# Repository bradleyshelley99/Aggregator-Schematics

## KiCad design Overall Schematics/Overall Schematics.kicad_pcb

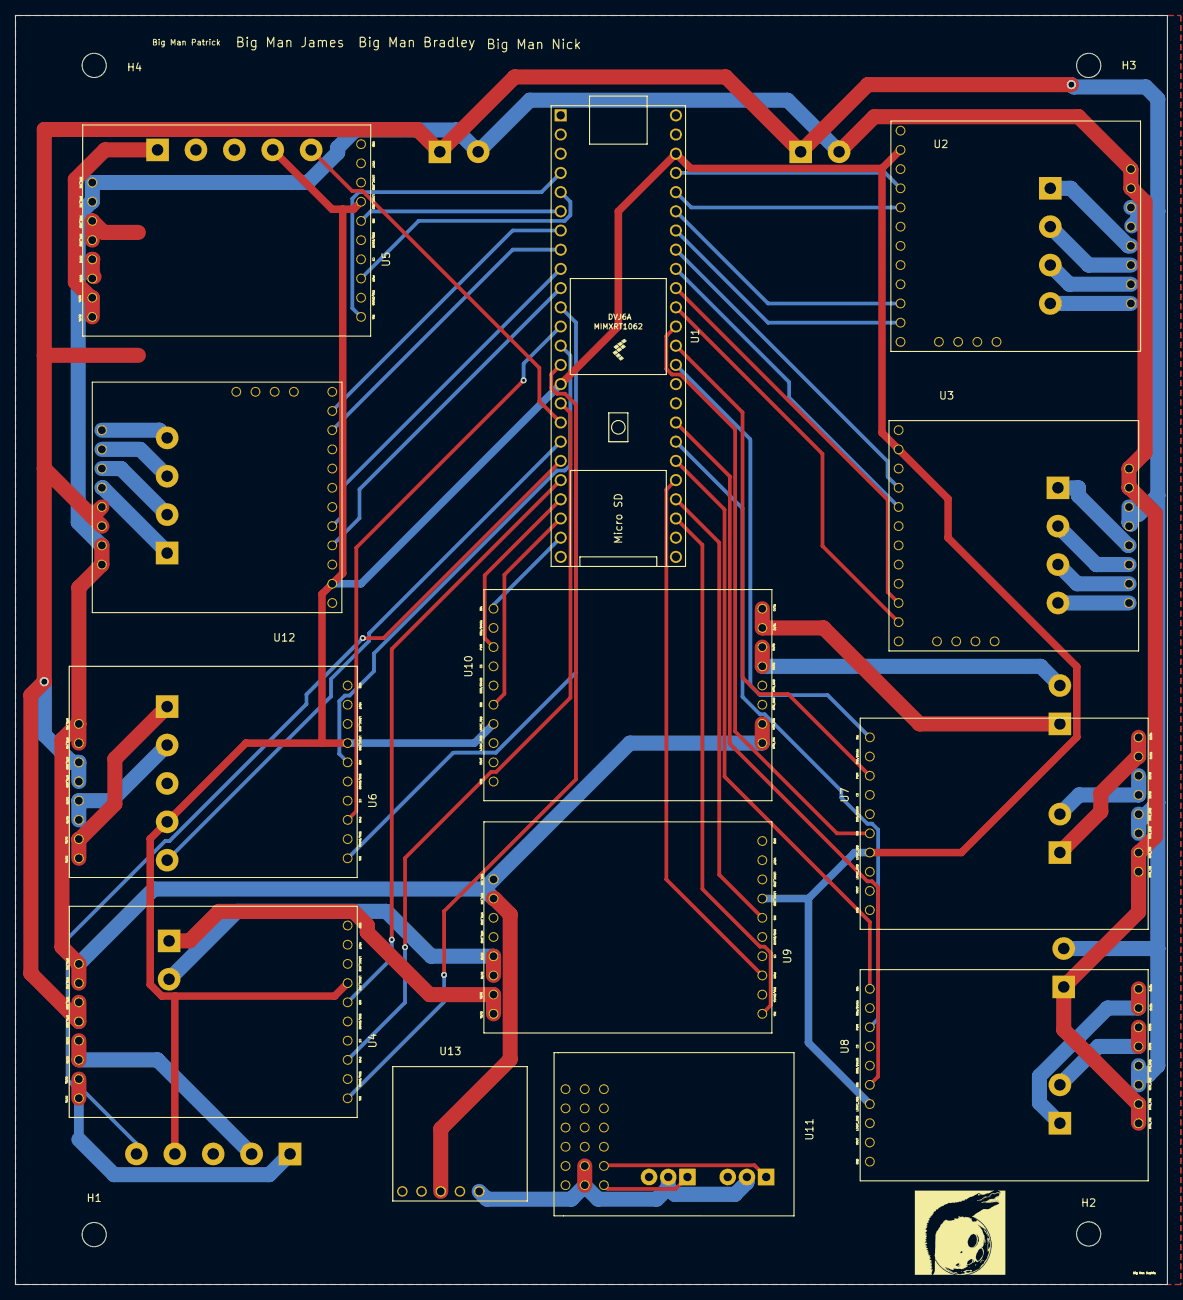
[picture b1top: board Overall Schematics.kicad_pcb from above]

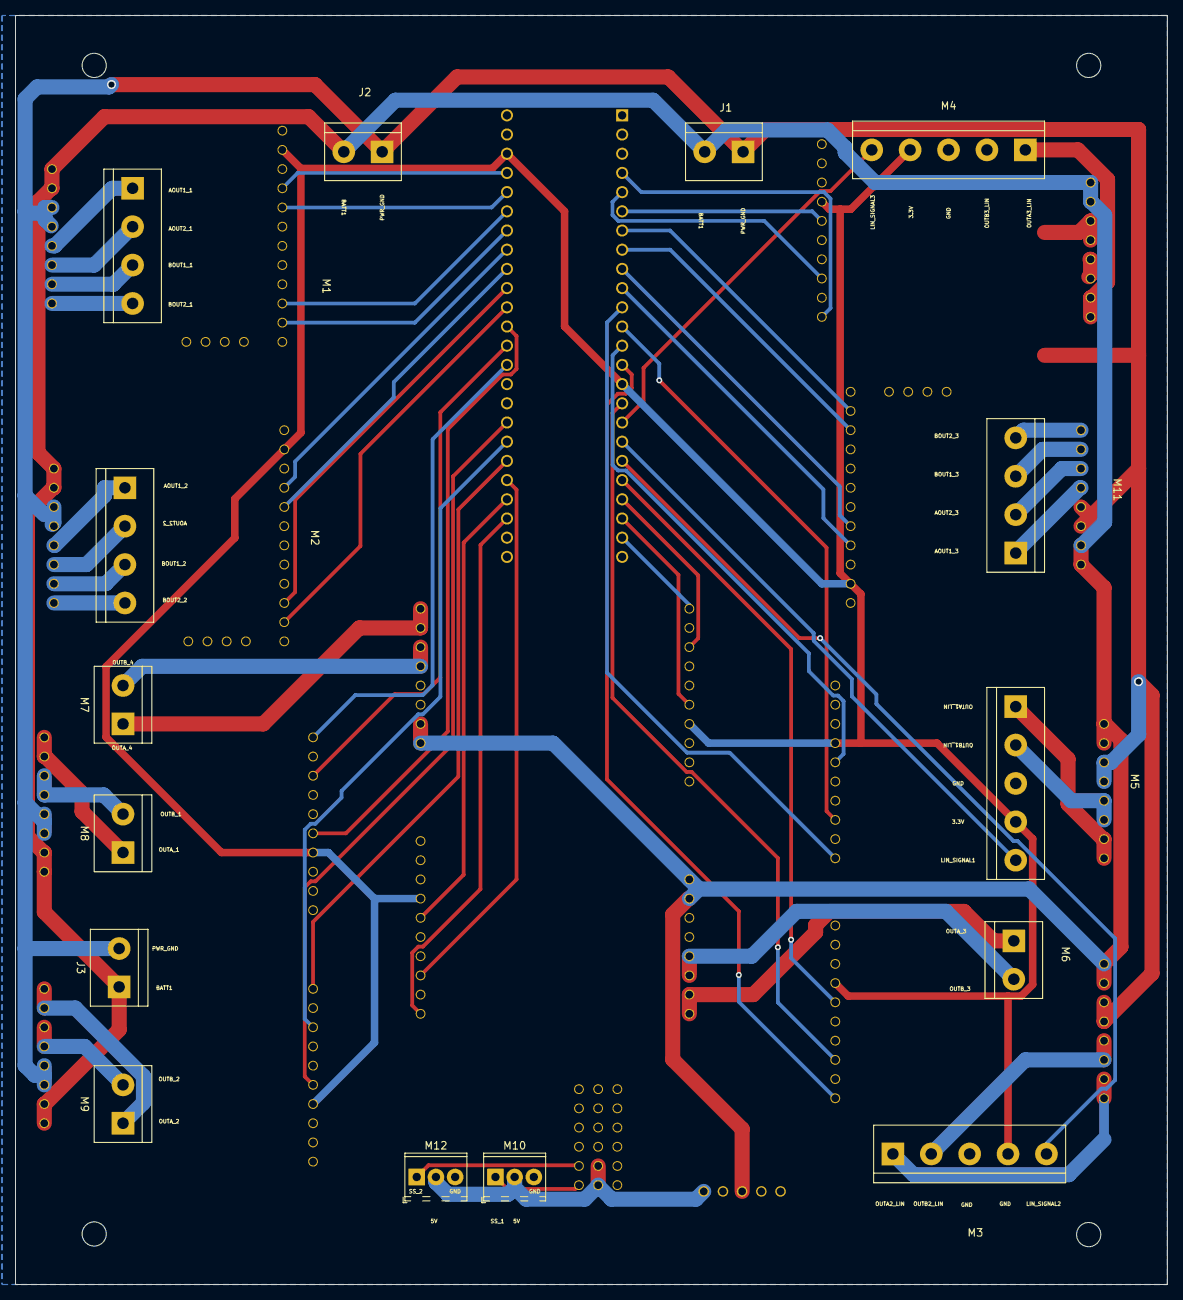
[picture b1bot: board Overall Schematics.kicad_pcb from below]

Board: 2 copper layers, 152.4 x 167.9 mm, 32 parts (15 on the bottom side), 69 nets.

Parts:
H1, H2, H3, H4: MountingHole; MountingHole_3.2mm_M3
J1: WattMeter1_Output; TerminalBlock_bornier-2_P5.08mm
J2: WattMeter2_Output; TerminalBlock_bornier-2_P5.08mm
J3: Intel_Buck_Converter_Input; TerminalBlock_bornier-2_P5.08mm
M1, M2, M11: Stepper_Motor_bipolar; TerminalBlock_bornier-4_P5.08mm
M3, M4, M5: LinActuator12V; TerminalBlock_bornier-5_P5.08mm
M6, M7, M8, M9: Motor_DC; TerminalBlock_bornier-2_P5.08mm
M10, M12: Motor_Servo; TerminalBlock_2.54_1x03_P2.54mm_Horizontal
U1: Teensy4.1; Teensy41
U2, U3, U12: 36v4SMD; StepperMotorDriver
U4, U5, U6, U7, U8, U9, U10: VNH52019; DCMotorDriver
U11: ServoDriver; ServoMotorDriver
U13: D24V22F5

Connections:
3.3V: M3.4 (Vin_EXC+), M4.4 (Vin_EXC+), M5.4 (Vin_EXC+), U1.46 (3V3), U2.2 (IOREF), U3.2 (IOREF), U4.7 (VDD), U5.7 (VDD), U6.7 (VDD), U7.7 (VDD), U8.7 (VDD), U9.7 (VDD), U10.7 (VDD), U12.2 (IOREF)
+5V: M10.2 (+), M12.2 (+), U11.7 (+_1), U11.8 (+_2), U13.5 (VOUT)
AOUT1_1: M1.1, U2.21 (AOUT1)
AOUT1_2: M2.1, U3.21 (AOUT1)
AOUT1_3: M11.1, U12.21 (AOUT1)
AOUT2_1: M1.2 (-), U2.22 (AOUT2)
AOUT2_2: M2.2 (-), U3.22 (AOUT2)
AOUT2_3: M11.2 (-), U12.22 (AOUT2)
BOUT1_1: M1.3, U2.23 (BOUT1)
BOUT1_2: M2.3, U3.23 (BOUT1)
BOUT1_3: M11.3, U12.23 (BOUT1)
BOUT2_1: M1.4, U2.24 (BOUT2)
BOUT2_2: M2.4, U3.24 (BOUT2)
BOUT2_3: M11.4, U12.24 (BOUT2)
Battery1_Positive24V: J1.2, J2.2, J3.1, U2.17 (VIN), U2.18 (VIN2), U3.17 (VIN), U3.18 (VIN2), U4.14 (VIN(5.5V-24V)), U5.14 (VIN(5.5V-24V)), U6.14 (VIN(5.5V-24V)), U7.14 (VIN(5.5V-24V)), U8.14 (VIN(5.5V-24V)), U9.14 (VIN(5.5V-24V)), U10.14 (VIN(5.5V-24V)), U12.17 (VIN), U12.18 (VIN2), U13.3 (VIN)
Battery_Neg: J1.1, J2.1, J3.2, U2.19 (GND), U2.20 (GND2), U3.19 (GND), U3.20 (GND2), U4.13 (GND), U5.13 (GND), U6.13 (GND), U7.13 (GND), U8.13 (GND), U9.13 (GND), U10.13 (GND), U12.19 (GND), U12.20 (GND2)
DIR_1: U1.44 (22_A8_CTX1), U2.5 (DIR/AIN2)
DIR_2: U1.40 (18_A4_SDA), U3.5 (DIR/AIN2)
DIR_3: U1.9 (7_RX2_OUT1A), U12.5 (DIR/AIN2)
GND: M3.3 (GND_EXC-), M4.3 (GND_EXC-), M5.3 (GND_EXC-), M10.3 (-), M12.3 (-), U1.1 (GND), U1.34 (GND), U1.47 (GND), U2.3 (GND), U3.3 (GND), U4.8 (GND), U5.8 (GND), U6.8 (GND), U7.8 (GND), U8.8 (GND), U9.8 (GND), U10.8 (GND), U11.13 (-_1), U11.14 (-_2), U12.3 (GND), U13.4 (GND)
INA_1: U1.35 (13_SCK_LED), U7.1 (INA)
INA_2: U1.30 (38_CS1_IN1), U8.1 (INA)
INA_3: U1.27 (35_TX8), U9.1 (INA)
INA_4: U1.23 (31_CTX3), U10.1 (INA)
INA_5: U1.11 (9_OUT1C), U6.1 (INA)
INA_6: U1.14 (12_MISO_MQSL), U4.1 (INA)
INA_7: U1.4 (2_OUT2), U5.1 (INA)
INB_1: U1.37 (15_A1_RX3_SPDIF_IN), U7.6 (INB)
INB_2: U1.32 (40_A16), U8.6 (INB)
INB_3: U1.28 (36_CS), U9.6 (INB)
INB_4: U1.22 (30_CRX3), U10.6 (INB)
INB_5: U1.13 (11_MOSI_CTX1), U6.6 (INB)
INB_6: U1.20 (28_RX7), U4.6 (INB)
INB_7: U1.6 (4_BCLK2), U5.6 (INB)
LIN_SIGNAL1: M5.5 (SIGNAL), U1.18 (26_A12_MOSI1)
LIN_SIGNAL2: M3.5 (SIGNAL), U1.19 (27_A13_SCK1)
LIN_SIGNAL3: M4.5 (SIGNAL), U1.17 (25_A11_RX6_SDA2)
OUTA1_LIN: M5.1 (Positive), U6.11 (OUTA)
OUTA2_LIN: M3.1 (Positive), U4.11 (OUTA)
OUTA3_LIN: M4.1 (Positive), U5.11 (OUTA)
OUTA_1: M8.1 (+), U7.11 (OUTA)
OUTA_2: M9.1 (+), U8.11 (OUTA)
OUTA_3: M6.1 (+), U9.11 (OUTA)
OUTA_4: M7.1 (+), U10.11 (OUTA)
OUTB1_LIN: M5.2 (Negative), U6.12 (OUTB)
OUTB2_LIN: M3.2 (Negative), U4.12 (OUTB)
OUTB3_LIN: M4.2 (Negative), U5.12 (OUTB)
OUTB_1: M8.2 (-), U7.12 (OUTB)
OUTB_2: M9.2 (-), U8.12 (OUTB)
OUTB_3: M6.2 (-), U9.12 (OUTB)
OUTB_4: M7.2 (-), U10.12 (OUTB)
PWM_1: U1.36 (14_A0_TX3_SPDIF_OUT), U7.3 (PWM)
PWM_2: U1.31 (39_MISO1_OUT1A), U8.3 (PWM)
PWM_3: U1.29 (37_CS), U9.3 (PWM)
PWM_4: U1.21 (29_TX7), U10.3 (PWM)
PWM_5: U1.12 (10_CS_MQSR), U6.3 (PWM)
PWM_6: U1.16 (24_A10_TX6_SCL2), U4.3 (PWM)
PWM_7: U1.5 (3_LRCLK2), U5.3 (PWM)
RESET_1: U1.42 (20_A6_TX5_LRCLK1), U2.11 (RESET)
RESET_2: U1.38 (16_A2_RX4_SCL1), U3.11 (RESET)
RESET_3: U1.7 (5_IN2), U12.11 (RESET)
SLEEP_1: U1.43 (21_A7_RX5_BCLK1), U2.10 (SLEEP)
SLEEP_2: U1.39 (17_A3_TX4_SDA1), U3.10 (SLEEP)
SLEEP_3: U1.8 (6_OUT1D), U12.10 (SLEEP)
SS_1: M10.1 (PWM), U11.1 (Signal_1)
SS_2: M12.1 (PWM), U11.2 (Signal_2)
STEP_1: U1.45 (23_A9_CRX1_MCLK1), U2.4 (STEP/AIN1)
STEP_2: U1.41 (19_A5_SCL), U3.4 (STEP/AIN1)
STEP_3: U1.10 (8_TX2_IN1), U12.4 (STEP/AIN1)

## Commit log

2022-03-02 Initial Commit with old files
2022-03-03 Schematic layout set needs routing
2022-03-03 DSN file
2022-03-03 4-Layer Setup
